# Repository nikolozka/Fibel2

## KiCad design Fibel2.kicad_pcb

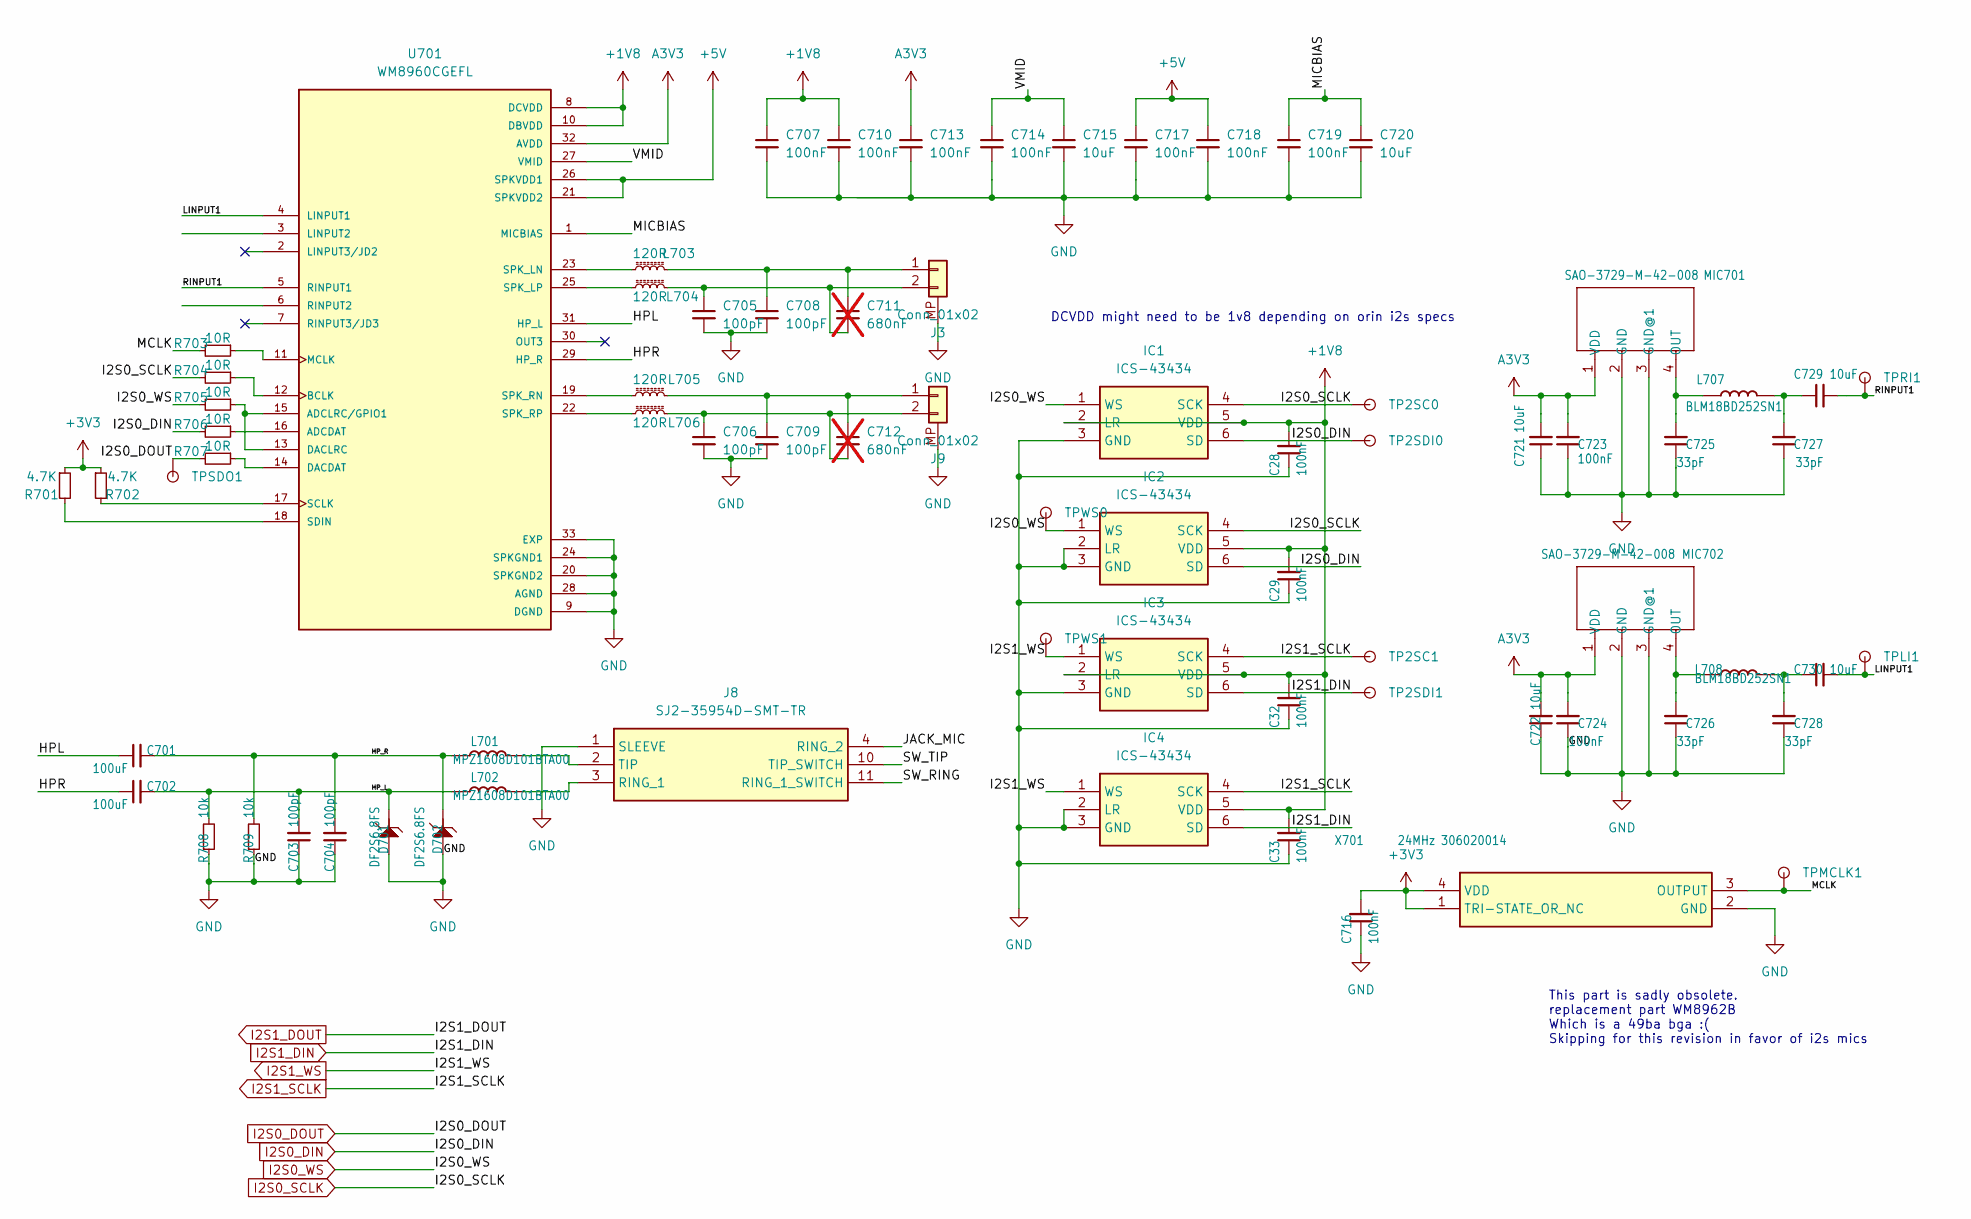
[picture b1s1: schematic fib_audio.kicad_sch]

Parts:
C28, C29, C32, C33, C707, C710, C713, C714, C716, C717, C718, C719, C723, C724: 100nF; C_0402_1005Metric
C701, C702: 100uF; C_0805_2012Metric
C703, C704, C705, C706, C708, C709: 100pF; C_0402_1005Metric
C711, C712: 680nF; C_0402_1005Metric; not fitted
C715, C720, C721, C722, C729, C730: 10uF; C_0603_1608Metric
C725, C726, C727, C728: 33pF; C_0402_1005Metric
D701, D702: DF2S6.8FS; D_SOD-923
IC1, IC2, IC3, IC4: ICS-43434; ICS43434; Mouser Part Number 410-ICS-43434
J3, J9: Conn_01x02; JST_PH_S2B-PH-SM4-TB_1x02-1MP_P2.00mm_Horizontal
J8: SJ2-35954D-SMT-TR; SJ235954DSMTTR; Mouser Part Number 490-SJ2-35954DSMT-TR
L701, L702: MPZ1608D101BTA00; L_0603_1608Metric
L703, L704, L705, L706: 120R; L_0603_1608Metric
L707, L708: BLM18BD252SN1; L_0603_1608Metric
MIC701, MIC702: SAO-3729-M-42-008; MIC_Respeaker
R701, R702: 4.7K; R_0402_1005Metric
R703, R704, R705, R706, R707: 10R; R_0402_1005Metric
R708, R709: 10k; R_0402_1005Metric
TP2SC0, TP2SC1, TP2SDI0, TP2SDI1: TestPoint; TestPoint_Pad_D1.0mm
TPLI1: TestPoint; TestPoint_Pad_D1.0mm
TPMCLK1: TestPoint; TestPoint_Pad_D1.0mm
TPRI1: TestPoint; TestPoint_Pad_D1.0mm
TPSDO1: TestPoint; TestPoint_Pad_D1.0mm
TPWS0, TPWS1: TestPoint; TestPoint_Pad_D1.0mm
U701: WM8960CGEFL; QFN50P500X500X100-33N
X701: 24MHz 306020014; ECS2520MV; Mouser Part Number 520-327ATQ2520MVBSTR

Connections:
+1V8: C28.2, C29.2, C32.2, C33.2, C707.1, C710.1, IC1.2 (LR), IC1.5 (VDD), IC2.5 (VDD), IC3.2 (LR), IC3.5 (VDD), IC4.5 (VDD), U701.8 (DCVDD), U701.10 (DBVDD); also elsewhere on the board
+3V3: C716.2, R701.1, R702.1, X701.1 (TRI-STATE_OR_NC), X701.4 (VDD); also elsewhere on the board
+5V: C717.1, C718.1, U701.21 (SPKVDD2), U701.26 (SPKVDD1); also elsewhere on the board
/Audio/HPL: C701.1, U701.31 (HP_L)
/Audio/HPR: C702.1, U701.29 (HP_R)
/Audio/HP_L: C702.2, C703.2, D701.1 (2), L702.1, R708.2
/Audio/HP_R: C701.2, C704.2, D702.1 (2), L701.1, R709.2
/Audio/JACK_MIC: J8.4 (RING_2)
/Audio/LINPUT1: C730.2, TPLI1.1, U701.4 (LINPUT1)
/Audio/MCLK: R703.2, TPMCLK1.1, X701.3 (OUTPUT)
/Audio/MICBIAS: C719.1, C720.1, U701.1 (MICBIAS)
/Audio/RINPUT1: C729.2, TPRI1.1, U701.5 (RINPUT1)
/Audio/SW_RING: J8.11 (RING_1_SWITCH)
/Audio/SW_TIP: J8.10 (TIP_SWITCH)
/Audio/VMID: C714.1, C715.1, U701.27 (VMID)
A3V3: C713.1, C721.2, C722.2, C723.2, C724.2, MIC701.1 (VDD), MIC702.1 (VDD), U701.32 (AVDD); also elsewhere on the board
GND: C28.1, C29.1, C32.1, C33.1, C703.1, C704.1, C705.2, C706.2, C707.2, C708.2, C709.2, C710.2, C713.2, C714.2, C715.2, C716.1, C717.2, C718.2, C719.2, C720.2, C721.1, C722.1, C723.1, C724.1, C725.1, C726.1, C727.1, C728.1, D701.2 (1), D702.2 (1), IC1.3 (GND), IC2.2 (LR), IC2.3 (GND), IC3.3 (GND), IC4.2 (LR), IC4.3 (GND), J3.MP, J8.1 (SLEEVE), J9.MP, MIC701.2 (GND), MIC701.3 (GND@1), MIC702.2 (GND), MIC702.3 (GND@1), R708.1, R709.1, U701.9 (DGND), U701.20 (SPKGND2), U701.24 (SPKGND1), U701.28 (AGND), U701.33 (EXP), X701.2 (GND); also elsewhere on the board
I2S0_DIN: IC1.6 (SD), IC2.6 (SD), R706.2, TP2SDI0.1; also elsewhere on the board
I2S0_DOUT: R707.2, TPSDO1.1; also elsewhere on the board
I2S0_SCLK: IC1.4 (SCK), IC2.4 (SCK), R704.2, TP2SC0.1; also elsewhere on the board
I2S0_WS: IC1.1 (WS), IC2.1 (WS), R705.2, TPWS0.1; also elsewhere on the board
I2S1_DIN: IC3.6 (SD), IC4.6 (SD), TP2SDI1.1; also elsewhere on the board
I2S1_SCLK: IC3.4 (SCK), IC4.4 (SCK), TP2SC1.1; also elsewhere on the board
I2S1_WS: IC3.1 (WS), IC4.1 (WS), TPWS1.1; also elsewhere on the board
unnamed: C727.2, C729.1, L707.2
unnamed: C728.2, C730.1, L708.2
unnamed: C708.1, C711.1, J3.1, L703.2
unnamed: C705.1, C711.2, J3.2, L704.2
unnamed: J8.3 (RING_1), L702.2
unnamed: J8.2 (TIP), L701.2
unnamed: C709.1, C712.1, J9.1, L705.2
unnamed: C706.1, C712.2, J9.2, L706.2
unnamed: C725.2, L707.1, MIC701.4 (OUT)
unnamed: C726.2, L708.1, MIC702.4 (OUT)
unnamed: R706.1, U701.16 (ADCDAT)
unnamed: R705.1, U701.13 (DACLRC), U701.15 (ADCLRC/GPIO1)
unnamed: R704.1, U701.12 (BCLK)
unnamed: R707.1, U701.14 (DACDAT)
unnamed: R703.1, U701.11 (MCLK)
unnamed: R702.2, U701.17 (SCLK)
unnamed: R701.2, U701.18 (SDIN)
unnamed: L703.1, U701.23 (SPK_LN)
unnamed: L704.1, U701.25 (SPK_LP)
unnamed: L705.1, U701.19 (SPK_RN)
unnamed: L706.1, U701.22 (SPK_RP)

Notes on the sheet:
DCVDD might need to be 1v8 depending on orin i2s specs
This part is sadly obsolete. replacement part WM8962B Which is a 49ba bga :( Skipping for this revision in favor of i2s mics

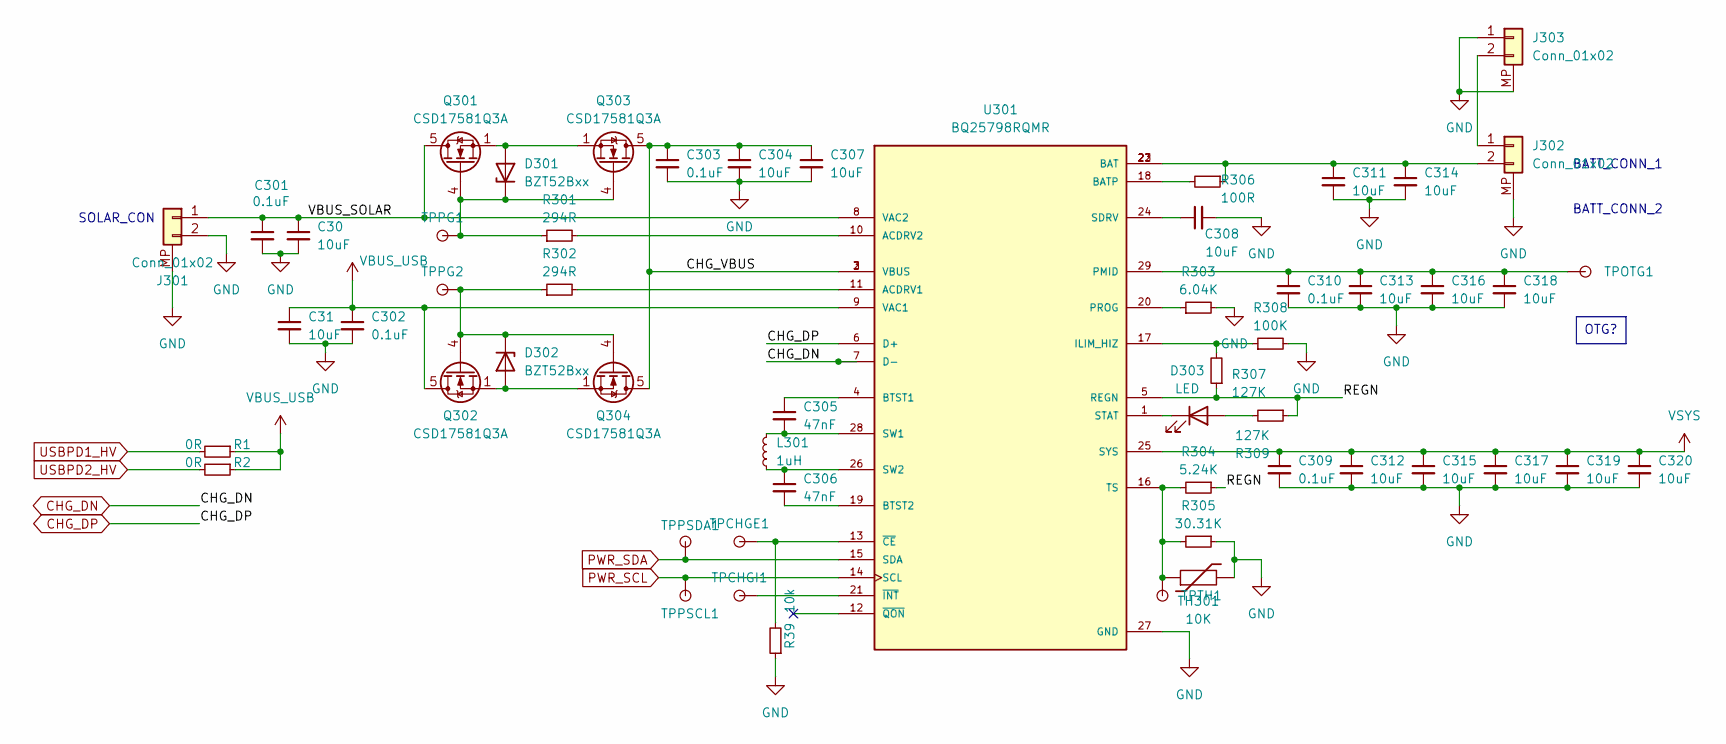
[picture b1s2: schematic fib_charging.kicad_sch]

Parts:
C30, C31, C304, C307, C308, C311, C312, C313, C314, C315, C316, C317, C318, C319, C320: 10uF; C_0603_1608Metric
C301, C302, C303, C309, C310: 0.1uF; C_0402_1005Metric
C305, C306: 47nF; C_0402_1005Metric
D301, D302: BZT52Bxx; D_SOD-123F
D303: LED; LED_0603_1608Metric
J301, J302, J303: Conn_01x02; JST_PH_S2B-PH-SM4-TB_1x02-1MP_P2.00mm_Horizontal
L301: 1uH; SPM6530
Q301, Q302, Q303, Q304: CSD17581Q3A; VSON-8_3.3x3.3mm_P0.65mm_NexFET
R1, R2: 0R; R_0603_1608Metric
R39: 10K; R_0402_1005Metric; Tolerance 1%; MPN CR0402-FX-1002GLF
R301, R302: 294R; R_0402_1005Metric
R303: 6.04K; R_0402_1005Metric
R304: 5.24K; R_0402_1005Metric
R305: 30.31K; R_0402_1005Metric
R306: 100R; R_0402_1005Metric
R307, R309: 127K; R_0402_1005Metric
R308: 100K; R_0402_1005Metric
TH301: 10K; R_0402_1005Metric
TPCHGE1: TestPoint; TestPoint_Pad_D1.0mm
TPCHGI1: TestPoint; TestPoint_Pad_D1.0mm
TPOTG1: TestPoint; TestPoint_Pad_D1.0mm
TPPG1, TPPG2: TestPoint; TestPoint_Pad_D1.0mm
TPPSCL1: TestPoint; TestPoint_Pad_D1.0mm
TPPSDA1: TestPoint; TestPoint_Pad_D1.0mm
TPTH1: TestPoint; TestPoint_Pad_D1.0mm
U301: BQ25798RQMR; IBQ25798RQMR

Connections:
/Charging/CHG_VBUS: C303.1, C304.1, C307.1, Q303.5 (D), Q304.5 (D), U301.2 (VBUS), U301.3 (VBUS)
/Charging/REGN: R304.1, R307.1, R309.1, U301.5 (REGN)
/Charging/VBUS_SOLAR: C30.1, C301.1, J301.1, Q301.5 (D), U301.8 (VAC2)
CHG_DN: U301.7 (D-); also elsewhere on the board
CHG_DP: U301.6 (D+); also elsewhere on the board
GND: C30.2, C31.2, C301.2, C302.2, C303.2, C304.2, C307.2, C308.2, C309.2, C310.2, C311.2, C312.2, C313.2, C314.2, C315.2, C316.2, C317.2, C318.2, C319.2, C320.2, J301.2, J301.MP, J302.MP, J303.1, J303.MP, R39.1, R303.2, R305.1, R308.2, TH301.2, U301.27 (GND); also elsewhere on the board
unnamed: D301.2 (A), Q301.1 (S), Q301.2 (S), Q301.3 (S), Q303.1 (S), Q303.2 (S), Q303.3 (S)
unnamed: D301.1 (K), Q301.4 (G), Q303.4 (G), R301.1, TPPG1.1
unnamed: D302.2 (A), Q302.1 (S), Q302.2 (S), Q302.3 (S), Q304.1 (S), Q304.2 (S), Q304.3 (S)
unnamed: D302.1 (K), Q302.4 (G), Q304.4 (G), R302.1, TPPG2.1
unnamed: D303.2 (A), R309.2
unnamed: D303.1 (K), U301.1 (STAT)
unnamed: J302.1, J303.2
unnamed: C311.1, C314.1, J302.2, R306.1, U301.22 (BAT), U301.23 (BAT)
unnamed: R302.2, U301.11 (ACDRV1)
unnamed: R301.2, U301.10 (ACDRV2)
unnamed: R306.2, U301.18 (BATP)
unnamed: C305.1, U301.4 (BTST1)
unnamed: C306.2, U301.19 (BTST2)
unnamed: R307.2, R308.1, U301.17 (ILIM_HIZ)
unnamed: C310.1, C313.1, C316.1, C318.1, TPOTG1.1, U301.29 (PMID)
unnamed: R303.1, U301.20 (PROG)
unnamed: C308.1, U301.24 (SDRV)
unnamed: C305.2, L301.2, U301.28 (SW1)
unnamed: C306.1, L301.1, U301.26 (SW2)
unnamed: R304.2, R305.2, TH301.1, TPTH1.1, U301.16 (TS)
unnamed: R39.2, TPCHGE1.1, U301.13 (~CE)
unnamed: TPCHGI1.1, U301.21 (~INT)
PWR_SCL: TPPSCL1.1, U301.14 (SCL); also elsewhere on the board
PWR_SDA: TPPSDA1.1, U301.15 (SDA); also elsewhere on the board
USBPD1_HV: R1.2; also elsewhere on the board
USBPD2_HV: R2.2; also elsewhere on the board
VBUS_USB: C31.1, C302.1, Q302.5 (D), R1.1, R2.1, U301.9 (VAC1); also elsewhere on the board
VSYS: C309.1, C312.1, C315.1, C317.1, C319.1, C320.1, U301.25 (SYS); also elsewhere on the board

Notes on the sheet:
OTG?
BATT_CONN_2
SOLAR_CON
BATT_CONN_1

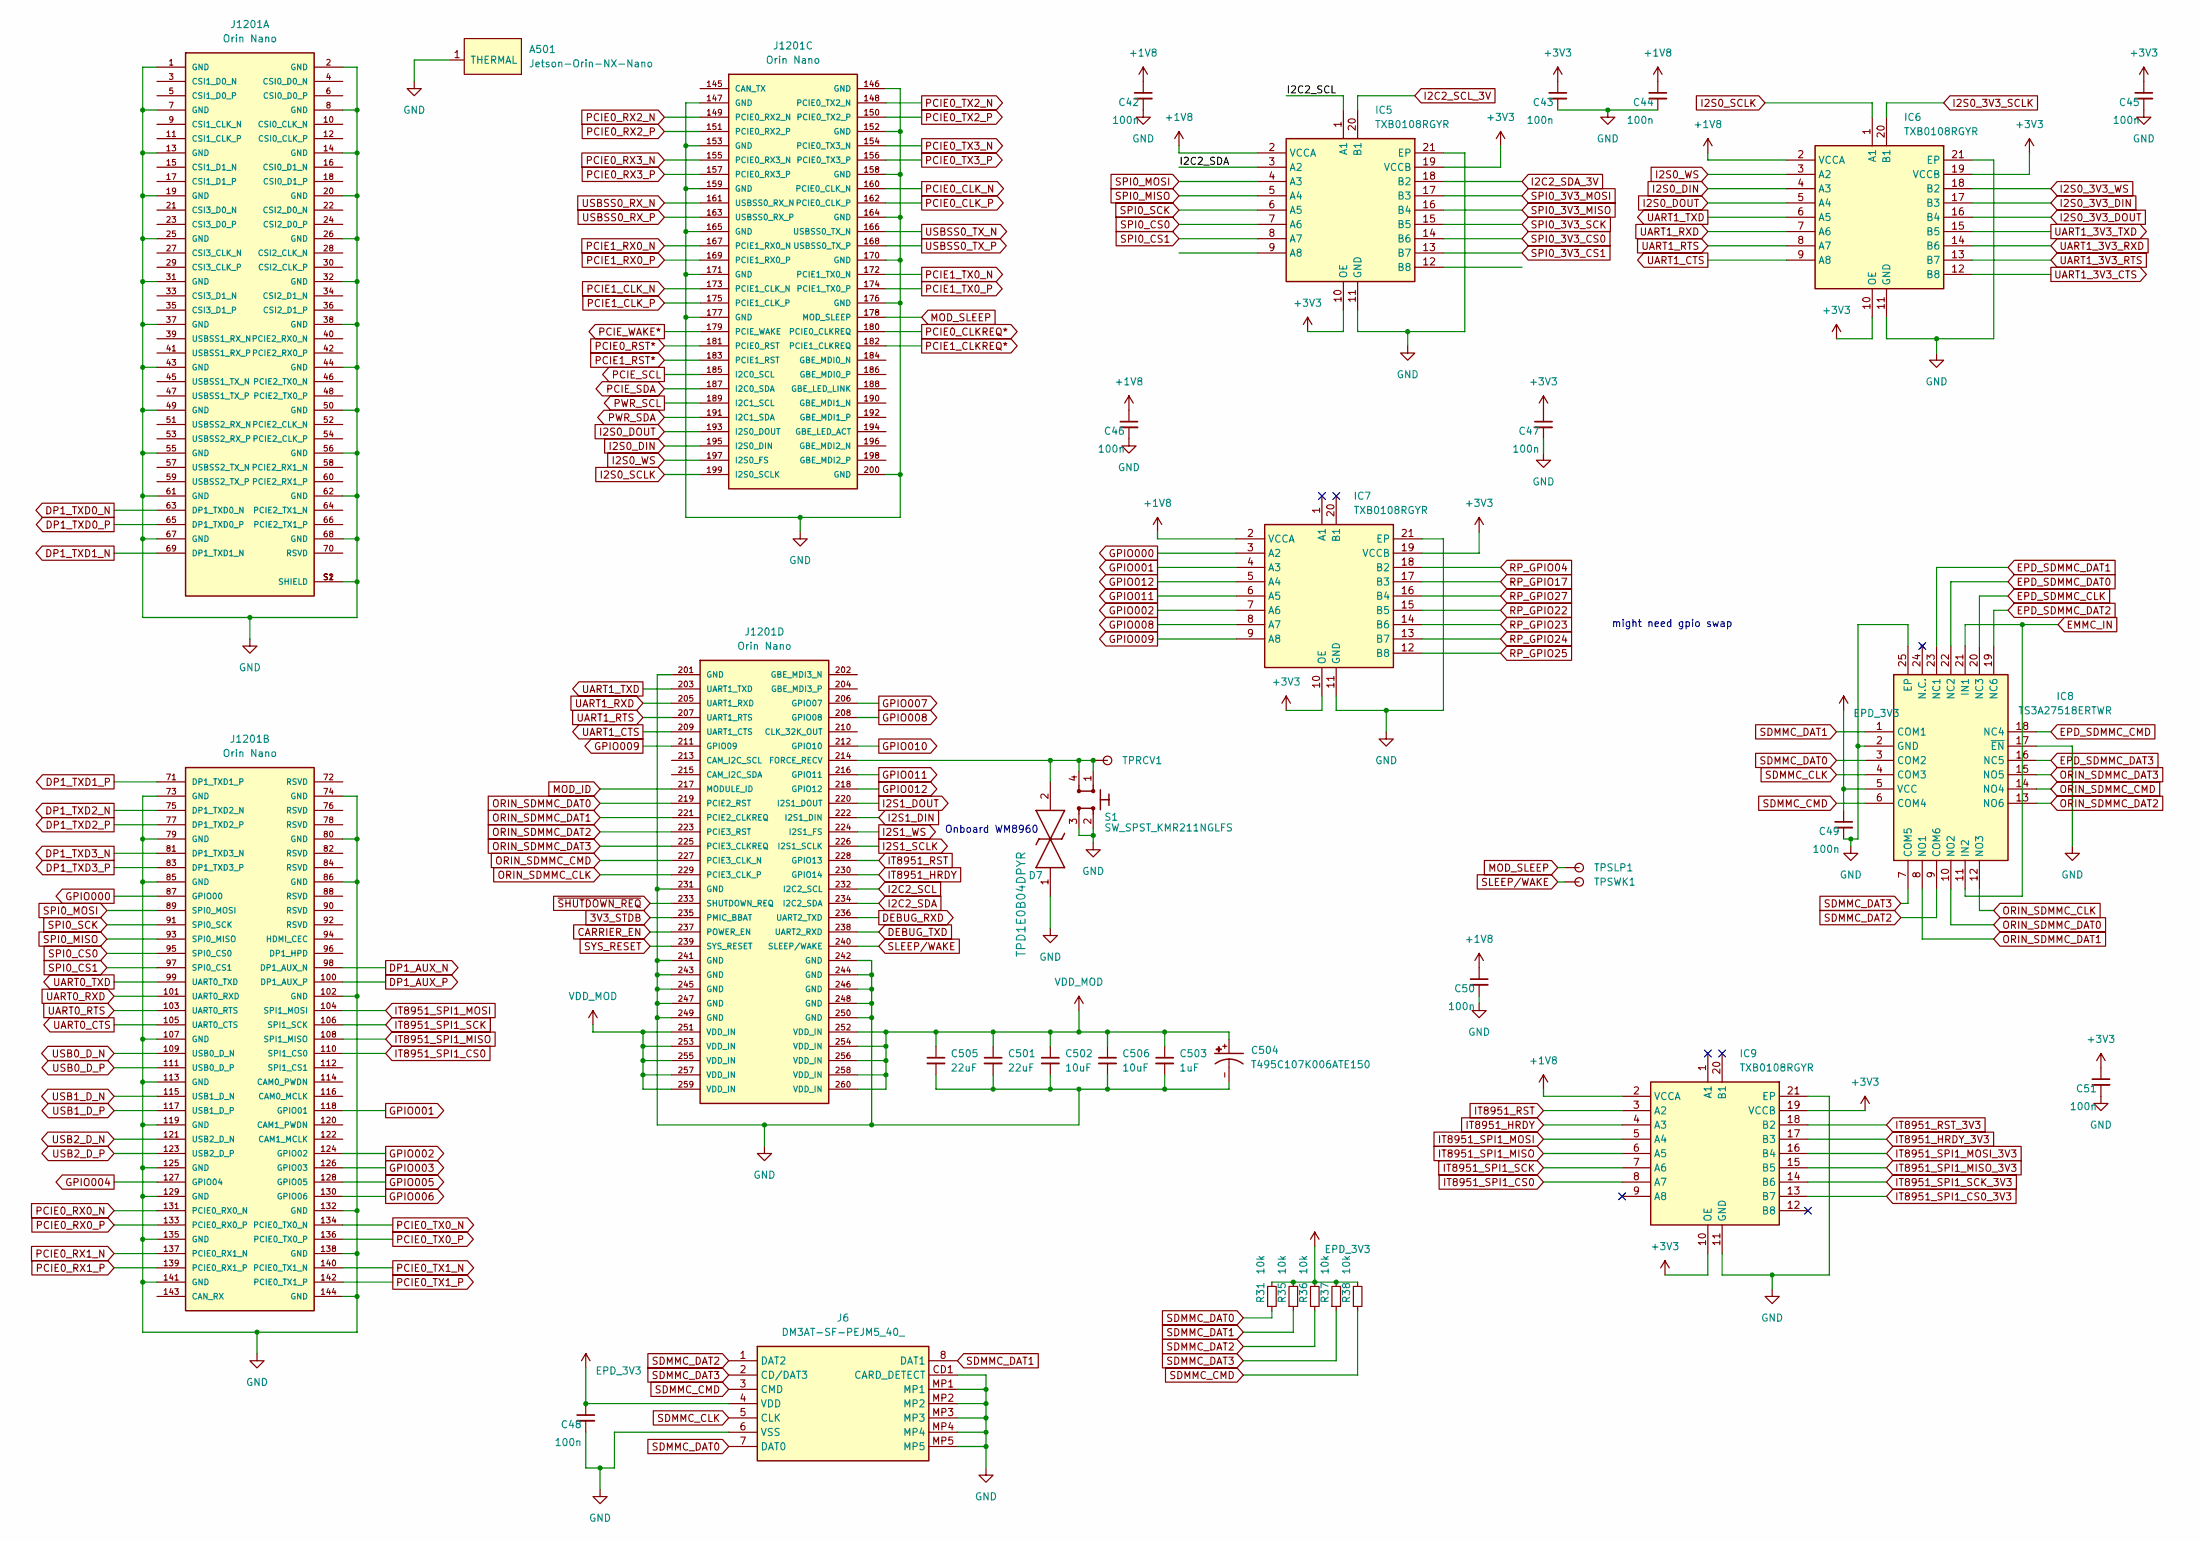
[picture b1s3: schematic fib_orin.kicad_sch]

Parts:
A501: Jetson-Orin-NX-Nano; jetson-orin-nx-nano-module; MPN 900-13767-0000-000
C42, C43, C44, C45, C46, C47, C48, C49, C50, C51: 100nF; C_0402_1005Metric; Voltage 50V; MPN GRM155R61H104KE14D
C501, C505: 22uF; C_0805_2012Metric
C502, C506: 10uF; C_0603_1608Metric
C503: 1uF; C_0402_1005Metric
C504: T495C107K006ATE150; CAPMP6032X250
D7: TPD1E0B04_XDFN-2; TPD1E0B04DPYT; MPN TPD1E0B04DPYR; Mouser Part Number 595-TPD1E0B04DPYT
IC5, IC6, IC7, IC9: TXB0108RGYR; TXB0108; Mouser Part Number 595-TXB0108RGYR
IC8: TS3A27518ERTWR; QFN50P400X400X80-25N; Mouser Part Number 595-TS3A27518ERTWR
J6: DM3AT-SF-PEJM5_40_; DM3ATSFPEJM540; Mouser Part Number 798-DM3AT-SF-PEJM540
J1201: Orin Nano; SODIMM_REVERSED
R31, R35, R36, R37, R38: 10K; R_0402_1005Metric; Tolerance 1%; MPN CR0402-FX-1002GLF
S1: SW_SPST_KMR211NGLFS; KMR211NGLFS; MPN KMR211NGLFS
TPRCV1: TestPoint; TestPoint_Pad_D1.0mm
TPSLP1: TestPoint; TestPoint_Pad_D1.0mm
TPSWK1: TestPoint; TestPoint_Pad_D1.0mm

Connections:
3V3_STDB: J1201.235 (PMIC_BBAT); also elsewhere on the board
+1V8: C42.1, C44.1, C46.1, C50.1, IC5.2 (VCCA), IC6.2 (VCCA), IC7.2 (VCCA), IC9.2 (VCCA); also elsewhere on the board
+3V3: C43.1, C45.1, C47.1, C51.1, IC5.10 (OE), IC5.19 (VCCB), IC6.10 (OE), IC6.19 (VCCB), IC7.10 (OE), IC7.19 (VCCB), IC9.10 (OE), IC9.19 (VCCB); also elsewhere on the board
CARRIER_EN: J1201.237 (POWER_EN); also elsewhere on the board
DEBUG_RXD: J1201.236 (UART2_TXD); also elsewhere on the board
DEBUG_TXD: J1201.238 (UART2_RXD); also elsewhere on the board
DP1_AUX_N: J1201.98 (DP1_AUX_N); also elsewhere on the board
DP1_AUX_P: J1201.100 (DP1_AUX_P); also elsewhere on the board
DP1_TXD0_N: J1201.63 (DP1_TXD0_N); also elsewhere on the board
DP1_TXD0_P: J1201.65 (DP1_TXD0_P); also elsewhere on the board
DP1_TXD1_N: J1201.69 (DP1_TXD1_N); also elsewhere on the board
DP1_TXD1_P: J1201.71 (DP1_TXD1_P); also elsewhere on the board
DP1_TXD2_N: J1201.75 (DP1_TXD2_N); also elsewhere on the board
DP1_TXD2_P: J1201.77 (DP1_TXD2_P); also elsewhere on the board
DP1_TXD3_N: J1201.81 (DP1_TXD3_N); also elsewhere on the board
DP1_TXD3_P: J1201.83 (DP1_TXD3_P); also elsewhere on the board
EMMC_IN: IC8.11 (IN2), IC8.21 (IN1); also elsewhere on the board
EPD_3V3: C48.1, C49.1, IC8.5 (VCC), J6.4 (VDD), R31.2, R35.2, R36.2, R37.2, R38.2; also elsewhere on the board
EPD_SDMMC_CLK: IC8.20 (NC3); also elsewhere on the board
EPD_SDMMC_CMD: IC8.18 (NC4); also elsewhere on the board
EPD_SDMMC_DAT0: IC8.22 (NC2); also elsewhere on the board
EPD_SDMMC_DAT1: IC8.23 (NC1); also elsewhere on the board
EPD_SDMMC_DAT2: IC8.19 (NC6); also elsewhere on the board
EPD_SDMMC_DAT3: IC8.16 (NC5); also elsewhere on the board
GND: A501.1 (THERMAL), C42.2, C43.2, C44.2, C45.2, C46.2, C47.2, C48.2, C49.2, C50.2, C51.2, C501.2, C502.2, C503.2, C504.-, C505.2, C506.2, D7.1, IC5.11 (GND), IC5.21 (EP), IC6.11 (GND), IC6.21 (EP), IC7.11 (GND), IC7.21 (EP), IC8.2 (GND), IC8.17 (~EN), IC8.25 (EP), IC9.11 (GND), IC9.21 (EP), J6.6 (VSS), J6.CD1 (CARD_DETECT), J6.MP1, J6.MP2, J6.MP3, J6.MP4, J6.MP5, J1201.1 (GND), J1201.2 (GND), J1201.7 (GND), J1201.8 (GND), J1201.13 (GND), J1201.14 (GND), J1201.19 (GND), J1201.20 (GND), J1201.25 (GND), J1201.26 (GND), J1201.31 (GND), J1201.32 (GND), J1201.37 (GND), J1201.38 (GND), J1201.43 (GND), J1201.44 (GND), J1201.49 (GND), J1201.50 (GND), J1201.55 (GND), J1201.56 (GND), J1201.61 (GND), J1201.62 (GND), J1201.67 (GND), J1201.68 (GND), J1201.73 (GND), J1201.74 (GND), J1201.79 (GND), J1201.80 (GND), J1201.85 (GND), J1201.86 (GND), J1201.102 (GND), J1201.107 (GND), J1201.113 (GND), J1201.119 (GND), J1201.125 (GND), J1201.129 (GND), J1201.132 (GND), J1201.135 (GND), J1201.138 (GND), J1201.141 (GND), J1201.144 (GND), J1201.146 (GND), J1201.147 (GND), J1201.152 (GND), J1201.153 (GND), J1201.158 (GND), J1201.159 (GND), J1201.164 (GND), J1201.165 (GND), J1201.170 (GND), J1201.171 (GND), J1201.176 (GND), J1201.177 (GND), J1201.200 (GND), J1201.201 (GND), J1201.231 (GND), J1201.241 (GND), J1201.242 (GND), J1201.243 (GND), J1201.244 (GND), J1201.245 (GND), J1201.246 (GND), J1201.247 (GND), J1201.248 (GND), J1201.249 (GND), J1201.250 (GND), J1201.S1 (SHIELD), J1201.S2 (SHIELD), S1.2, S1.3; also elsewhere on the board
GPIO000: IC7.3 (A2), J1201.87 (GPIO00)
GPIO001: IC7.4 (A3), J1201.118 (GPIO01)
GPIO002: IC7.7 (A6), J1201.124 (GPIO02)
GPIO003: J1201.126 (GPIO03); also elsewhere on the board
GPIO004: J1201.127 (GPIO04)
GPIO005: J1201.128 (GPIO05); also elsewhere on the board
GPIO006: J1201.130 (GPIO06); also elsewhere on the board
GPIO007: J1201.206 (GPIO07); also elsewhere on the board
GPIO008: IC7.8 (A7), J1201.208 (GPIO08)
GPIO009: IC7.9 (A8), J1201.211 (GPIO09)
GPIO010: J1201.212 (GPIO10); also elsewhere on the board
GPIO011: IC7.6 (A5), J1201.216 (GPIO11)
GPIO012: IC7.5 (A4), J1201.218 (GPIO12)
I2C2_SCL: IC5.1 (A1), J1201.232 (I2C2_SCL)
I2C2_SCL_3V: IC5.20 (B1); also elsewhere on the board
I2C2_SDA: IC5.3 (A2), J1201.234 (I2C2_SDA)
I2C2_SDA_3V: IC5.18 (B2); also elsewhere on the board
I2S0_3V3_DIN: IC6.17 (B3); also elsewhere on the board
I2S0_3V3_DOUT: IC6.16 (B4); also elsewhere on the board
I2S0_3V3_SCLK: IC6.20 (B1); also elsewhere on the board
I2S0_3V3_WS: IC6.18 (B2); also elsewhere on the board
I2S0_DIN: IC6.4 (A3), J1201.195 (I2S0_DIN); also elsewhere on the board
I2S0_DOUT: IC6.5 (A4), J1201.193 (I2S0_DOUT); also elsewhere on the board
I2S0_SCLK: IC6.1 (A1), J1201.199 (I2S0_SCLK); also elsewhere on the board
I2S0_WS: IC6.3 (A2), J1201.197 (I2S0_FS); also elsewhere on the board
I2S1_DIN: J1201.222 (I2S1_DIN); also elsewhere on the board
I2S1_DOUT: J1201.220 (I2S1_DOUT); also elsewhere on the board
I2S1_SCLK: J1201.226 (I2S1_SCLK); also elsewhere on the board
I2S1_WS: J1201.224 (I2S1_FS); also elsewhere on the board
IT8951_HRDY: IC9.4 (A3), J1201.230 (GPIO14)
IT8951_HRDY_3V3: IC9.17 (B3); also elsewhere on the board
IT8951_RST: IC9.3 (A2), J1201.228 (GPIO13)
IT8951_RST_3V3: IC9.18 (B2); also elsewhere on the board
IT8951_SPI1_CS0: IC9.8 (A7), J1201.110 (SPI1_CS0)
IT8951_SPI1_CS0_3V3: IC9.13 (B7); also elsewhere on the board
IT8951_SPI1_MISO: IC9.6 (A5), J1201.108 (SPI1_MISO)
IT8951_SPI1_MISO_3V3: IC9.15 (B5); also elsewhere on the board
IT8951_SPI1_MOSI: IC9.5 (A4), J1201.104 (SPI1_MOSI)
IT8951_SPI1_MOSI_3V3: IC9.16 (B4); also elsewhere on the board
IT8951_SPI1_SCK: IC9.7 (A6), J1201.106 (SPI1_SCK)
IT8951_SPI1_SCK_3V3: IC9.14 (B6); also elsewhere on the board
MOD_ID: J1201.217 (MODULE_ID)
MOD_SLEEP: J1201.178 (MOD_SLEEP), TPSLP1.1
unnamed: D7.2, J1201.214 (FORCE_RECV), S1.1, S1.4, TPRCV1.1
ORIN_SDMMC_CLK: IC8.12 (NO3), J1201.229 (PCIE3_CLK_P)
ORIN_SDMMC_CMD: IC8.14 (NO4), J1201.227 (PCIE3_CLK_N)
ORIN_SDMMC_DAT0: IC8.10 (NO2), J1201.219 (PCIE2_RST)
ORIN_SDMMC_DAT1: IC8.8 (NO1), J1201.221 (PCIE2_CLKREQ)
ORIN_SDMMC_DAT2: IC8.13 (NO6), J1201.223 (PCIE3_RST)
ORIN_SDMMC_DAT3: IC8.15 (NO5), J1201.225 (PCIE3_CLKREQ)
PCIE0_CLKREQ*: J1201.180 (PCIE0_CLKREQ); also elsewhere on the board
PCIE0_CLK_N: J1201.160 (PCIE0_CLK_N); also elsewhere on the board
PCIE0_CLK_P: J1201.162 (PCIE0_CLK_P); also elsewhere on the board
PCIE0_RST*: J1201.181 (PCIE0_RST); also elsewhere on the board
PCIE0_RX0_N: J1201.131 (PCIE0_RX0_N); also elsewhere on the board
PCIE0_RX0_P: J1201.133 (PCIE0_RX0_P); also elsewhere on the board
PCIE0_RX1_N: J1201.137 (PCIE0_RX1_N); also elsewhere on the board
PCIE0_RX1_P: J1201.139 (PCIE0_RX1_P); also elsewhere on the board
PCIE0_RX2_N: J1201.149 (PCIE0_RX2_N); also elsewhere on the board
PCIE0_RX2_P: J1201.151 (PCIE0_RX2_P); also elsewhere on the board
PCIE0_RX3_N: J1201.155 (PCIE0_RX3_N); also elsewhere on the board
PCIE0_RX3_P: J1201.157 (PCIE0_RX3_P); also elsewhere on the board
PCIE0_TX0_N: J1201.134 (PCIE0_TX0_N); also elsewhere on the board
PCIE0_TX0_P: J1201.136 (PCIE0_TX0_P); also elsewhere on the board
PCIE0_TX1_N: J1201.140 (PCIE0_TX1_N); also elsewhere on the board
PCIE0_TX1_P: J1201.142 (PCIE0_TX1_P); also elsewhere on the board
PCIE0_TX2_N: J1201.148 (PCIE0_TX2_N); also elsewhere on the board
PCIE0_TX2_P: J1201.150 (PCIE0_TX2_P); also elsewhere on the board
PCIE0_TX3_N: J1201.154 (PCIE0_TX3_N); also elsewhere on the board
PCIE0_TX3_P: J1201.156 (PCIE0_TX3_P); also elsewhere on the board
PCIE1_CLKREQ*: J1201.182 (PCIE1_CLKREQ); also elsewhere on the board
PCIE1_CLK_N: J1201.173 (PCIE1_CLK_N); also elsewhere on the board
PCIE1_CLK_P: J1201.175 (PCIE1_CLK_P); also elsewhere on the board
PCIE1_RST*: J1201.183 (PCIE1_RST); also elsewhere on the board
PCIE1_RX0_N: J1201.167 (PCIE1_RX0_N); also elsewhere on the board
PCIE1_RX0_P: J1201.169 (PCIE1_RX0_P); also elsewhere on the board
PCIE1_TX0_N: J1201.172 (PCIE1_TX0_N); also elsewhere on the board
PCIE1_TX0_P: J1201.174 (PCIE1_TX0_P); also elsewhere on the board
PCIE_SCL: J1201.185 (I2C0_SCL); also elsewhere on the board
PCIE_SDA: J1201.187 (I2C0_SDA); also elsewhere on the board
PCIE_WAKE*: J1201.179 (PCIE_WAKE); also elsewhere on the board
PWR_SCL: J1201.189 (I2C1_SCL); also elsewhere on the board
PWR_SDA: J1201.191 (I2C1_SDA); also elsewhere on the board
RP_GPIO04: IC7.18 (B2); also elsewhere on the board
RP_GPIO17: IC7.17 (B3); also elsewhere on the board
RP_GPIO22: IC7.15 (B5); also elsewhere on the board
RP_GPIO23: IC7.14 (B6); also elsewhere on the board
RP_GPIO24: IC7.13 (B7); also elsewhere on the board
RP_GPIO25: IC7.12 (B8); also elsewhere on the board
RP_GPIO27: IC7.16 (B4); also elsewhere on the board
SDMMC_CLK: IC8.4 (COM3), J6.5 (CLK)
SDMMC_CMD: IC8.6 (COM4), J6.3 (CMD), R38.1
SDMMC_DAT0: IC8.3 (COM2), J6.7 (DAT0), R31.1
SDMMC_DAT1: IC8.1 (COM1), J6.8 (DAT1), R35.1
SDMMC_DAT2: IC8.9 (COM6), J6.1 (DAT2), R36.1
SDMMC_DAT3: IC8.7 (COM5), J6.2 (CD/DAT3), R37.1
SLEEP/WAKE: J1201.240 (SLEEP/WAKE), TPSWK1.1
SPI0_3V3_CS0: IC5.14 (B6); also elsewhere on the board
SPI0_3V3_CS1: IC5.13 (B7); also elsewhere on the board
SPI0_3V3_MISO: IC5.16 (B4); also elsewhere on the board
SPI0_3V3_MOSI: IC5.17 (B3); also elsewhere on the board
SPI0_3V3_SCK: IC5.15 (B5); also elsewhere on the board
SPI0_CS0: IC5.7 (A6), J1201.95 (SPI0_CS0)
SPI0_CS1: IC5.8 (A7), J1201.97 (SPI0_CS1)
SPI0_MISO: IC5.5 (A4), J1201.93 (SPI0_MISO)
SPI0_MOSI: IC5.4 (A3), J1201.89 (SPI0_MOSI)
SPI0_SCK: IC5.6 (A5), J1201.91 (SPI0_SCK)
SYS_RESET: J1201.239 (SYS_RESET); also elsewhere on the board
UART0_CTS: J1201.105 (UART0_CTS); also elsewhere on the board
UART0_RTS: J1201.103 (UART0_RTS); also elsewhere on the board
UART0_RXD: J1201.101 (UART0_RXD); also elsewhere on the board
UART0_TXD: J1201.99 (UART0_TXD); also elsewhere on the board
UART1_3V3_CTS: IC6.12 (B8); also elsewhere on the board
UART1_3V3_RTS: IC6.13 (B7); also elsewhere on the board
UART1_3V3_RXD: IC6.14 (B6); also elsewhere on the board
UART1_3V3_TXD: IC6.15 (B5); also elsewhere on the board
UART1_CTS: IC6.9 (A8), J1201.209 (UART1_CTS)
UART1_RTS: IC6.8 (A7), J1201.207 (UART1_RTS)
UART1_RXD: IC6.7 (A6), J1201.205 (UART1_RXD)
UART1_TXD: IC6.6 (A5), J1201.203 (UART1_TXD)
USB0_D_N: J1201.109 (USB0_D_N); also elsewhere on the board
USB0_D_P: J1201.111 (USB0_D_P); also elsewhere on the board
USB1_D_N: J1201.115 (USB1_D_N); also elsewhere on the board
USB1_D_P: J1201.117 (USB1_D_P); also elsewhere on the board
USB2_D_N: J1201.121 (USB2_D_N); also elsewhere on the board
USB2_D_P: J1201.123 (USB2_D_P); also elsewhere on the board
USBSS0_RX_N: J1201.161 (USBSS0_RX_N); also elsewhere on the board
USBSS0_RX_P: J1201.163 (USBSS0_RX_P); also elsewhere on the board
USBSS0_TX_N: J1201.166 (USBSS0_TX_N); also elsewhere on the board
USBSS0_TX_P: J1201.168 (USBSS0_TX_P); also elsewhere on the board
VDD_MOD: C501.1, C502.1, C503.1, C504.+, C505.1, C506.1, J1201.251 (VDD_IN), J1201.252 (VDD_IN), J1201.253 (VDD_IN), J1201.254 (VDD_IN), J1201.255 (VDD_IN), J1201.256 (VDD_IN), J1201.257 (VDD_IN), J1201.258 (VDD_IN), J1201.259 (VDD_IN), J1201.260 (VDD_IN); also elsewhere on the board
~SHUTDOWN_REQ: J1201.233 (SHUTDOWN_REQ); also elsewhere on the board

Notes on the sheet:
Onboard WM8960
might need gpio swap

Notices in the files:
parts and their libraries:
License: Apache-2.0
